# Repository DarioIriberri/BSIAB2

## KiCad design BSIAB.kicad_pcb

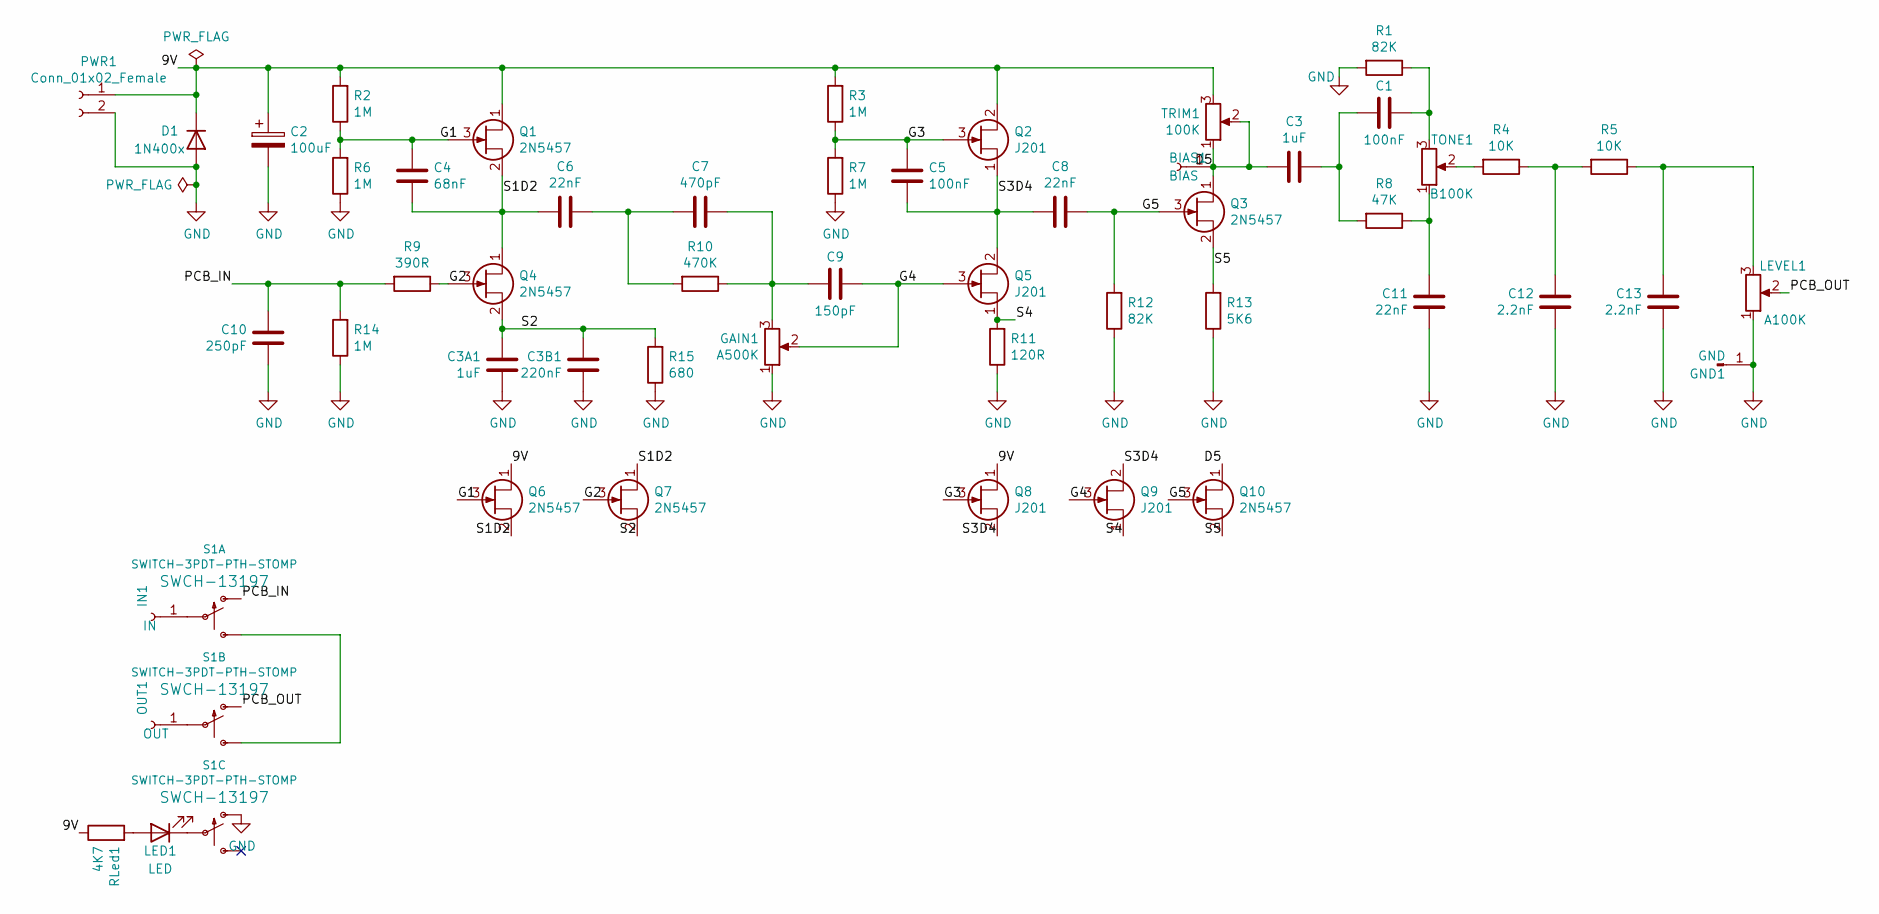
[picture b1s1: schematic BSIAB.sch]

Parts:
BIAS1: BIAS; PinHeader_1x01_P2.54mm_Vertical
C1: 100nF; C_Rect_L9.0mm_W3.4mm_P7.50mm_MKT
C2: 100uF; CP_Radial_D8.0mm_P2.50mm
C3, C3A1: 1uF; C_Rect_L9.0mm_W4.2mm_P7.50mm_MKT
C3B1: 220nF; C_Rect_L9.0mm_W4.2mm_P7.50mm_MKT
C4: 68nF; C_Rect_L9.0mm_W4.2mm_P7.50mm_MKT
C5: 100nF; C_Rect_L9.0mm_W4.2mm_P7.50mm_MKT
C6, C8, C11: 22nF; C_Rect_L9.0mm_W4.2mm_P7.50mm_MKT
C7: 470pF; C_Rect_L7.0mm_W3.5mm_P5.00mm
C9: 150pF; C_Rect_L7.0mm_W3.5mm_P5.00mm
C10: 250pF; C_Rect_L7.0mm_W3.5mm_P5.00mm
C12, C13: 2.2nF; C_Rect_L7.0mm_W3.5mm_P5.00mm
D1: 1N400x; D_A-405_P7.62mm_Horizontal
GAIN1: A500K; Potentiometer_Piher_T-16H_Single_Horizontal
GND1: GND; PinHeader_1x01_P2.54mm_Vertical
IN1: IN; PinHeader_1x01_P2.54mm_Vertical
LED1: LED; LED_D5.0mm
LEVEL1: A100K; Potentiometer_Piher_T-16H_Single_Horizontal
OUT1: OUT; PinHeader_1x01_P2.54mm_Vertical
PWR1: Conn_01x02_Female; JST_EH_B2B-EH-A_1x02_P2.50mm_Vertical
Q1, Q3, Q4: 2N5457; SOT-23
Q2, Q5: J201; SOT-23
Q6, Q7, Q10: 2N5457; TO-92
Q8, Q9: J201; TO-92
R1, R12: 82K; R_Axial_DIN0207_L6.3mm_D2.5mm_P7.62mm_Horizontal
R2, R3, R6, R7, R14: 1M; R_Axial_DIN0207_L6.3mm_D2.5mm_P7.62mm_Horizontal
R4, R5: 10K; R_Axial_DIN0207_L6.3mm_D2.5mm_P7.62mm_Horizontal
R8: 47K; R_Axial_DIN0207_L6.3mm_D2.5mm_P7.62mm_Horizontal
R9: 390R; R_Axial_DIN0207_L6.3mm_D2.5mm_P7.62mm_Horizontal
R10: 470K; R_Axial_DIN0207_L6.3mm_D2.5mm_P7.62mm_Horizontal
R11: 120R; R_Axial_DIN0207_L6.3mm_D2.5mm_P7.62mm_Horizontal
R13: 5K6; R_Axial_DIN0207_L6.3mm_D2.5mm_P7.62mm_Horizontal
R15: 680; R_Axial_DIN0207_L6.3mm_D2.5mm_P7.62mm_Horizontal
RLed1: 4K7; R_Axial_DIN0207_L6.3mm_D2.5mm_P7.62mm_Horizontal
S1: SWITCH-3PDT-PTH-STOMP; STOMP_SWITCH_3PDT
TONE1: B100K; Potentiometer_Piher_T-16H_Single_Horizontal
TRIM1: 100K; Potentiometer_Bourns_3296W_Vertical

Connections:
/9V: C2.1, D1.1 (K), PWR1.1, Q1.1 (D), Q2.2 (D), Q6.1 (D), Q8.1 (D), R2.2, R3.2, RLed1.1, TRIM1.3
/D5: BIAS1.1, C3.1, Q3.1 (D), Q10.1 (D), TRIM1.1, TRIM1.2
/G1: C4.1, Q1.3 (G), Q6.3 (G), R2.1, R6.2
/G2: Q4.3 (G), Q7.3 (G), R9.1
/G3: C5.1, Q2.3 (G), Q8.3 (G), R3.1, R7.2
/G4: C9.1, GAIN1.2, Q5.3 (G), Q9.3 (G)
/G5: C8.1, Q3.3 (G), Q10.3 (G), R12.2
/PCB_IN: C10.2, R9.2, R14.2, S1.P$1 (O)
/PCB_OUT: LEVEL1.2, S1.P$4 (O)
/S1D2: C4.2, C6.2, Q1.2 (S), Q4.1 (D), Q6.2 (S), Q7.1 (D)
/S2: C3A1.2, C3B1.2, Q4.2 (S), Q7.2 (S), R15.2
/S3D4: C5.2, C8.2, Q2.1 (S), Q5.2 (D), Q8.2 (S), Q9.2 (S)
/S4: Q5.1 (S), Q9.1 (D), R11.2
/S5: Q3.2 (S), Q10.2 (S), R13.2
GND: C2.2, C3A1.1, C3B1.1, C10.1, C11.1, C12.1, C13.1, D1.2 (A), GAIN1.1, GND1.1, LEVEL1.1, PWR1.2, R1.2, R6.1, R7.1, R11.1, R12.1, R13.1, R14.1, R15.1, S1.P$7 (O)
unnamed: C1.1, C3.2, R8.2
unnamed: C1.2, R1.1, TONE1.3
unnamed: C6.1, C7.2, R10.2
unnamed: C7.1, C9.2, GAIN1.3, R10.1
unnamed: C11.2, R8.1, TONE1.1
unnamed: C12.2, R4.1, R5.2
unnamed: C13.2, LEVEL1.3, R5.1
unnamed: IN1.1, S1.P$2
unnamed: LED1.1 (K), S1.P$8
unnamed: LED1.2 (A), RLed1.2
unnamed: OUT1.1, S1.P$5
unnamed: R4.2, TONE1.2
unnamed: S1.P$3 (S), S1.P$6 (S)

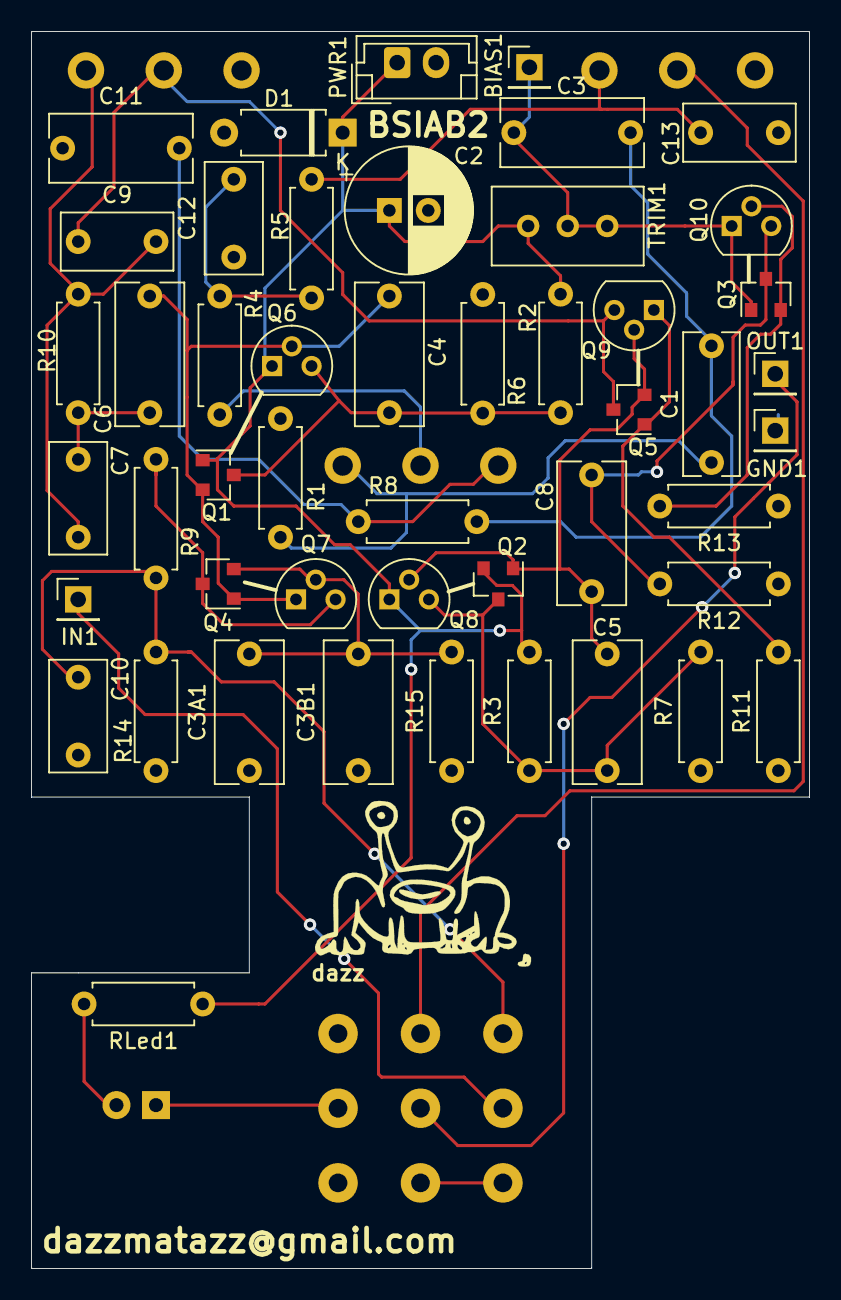
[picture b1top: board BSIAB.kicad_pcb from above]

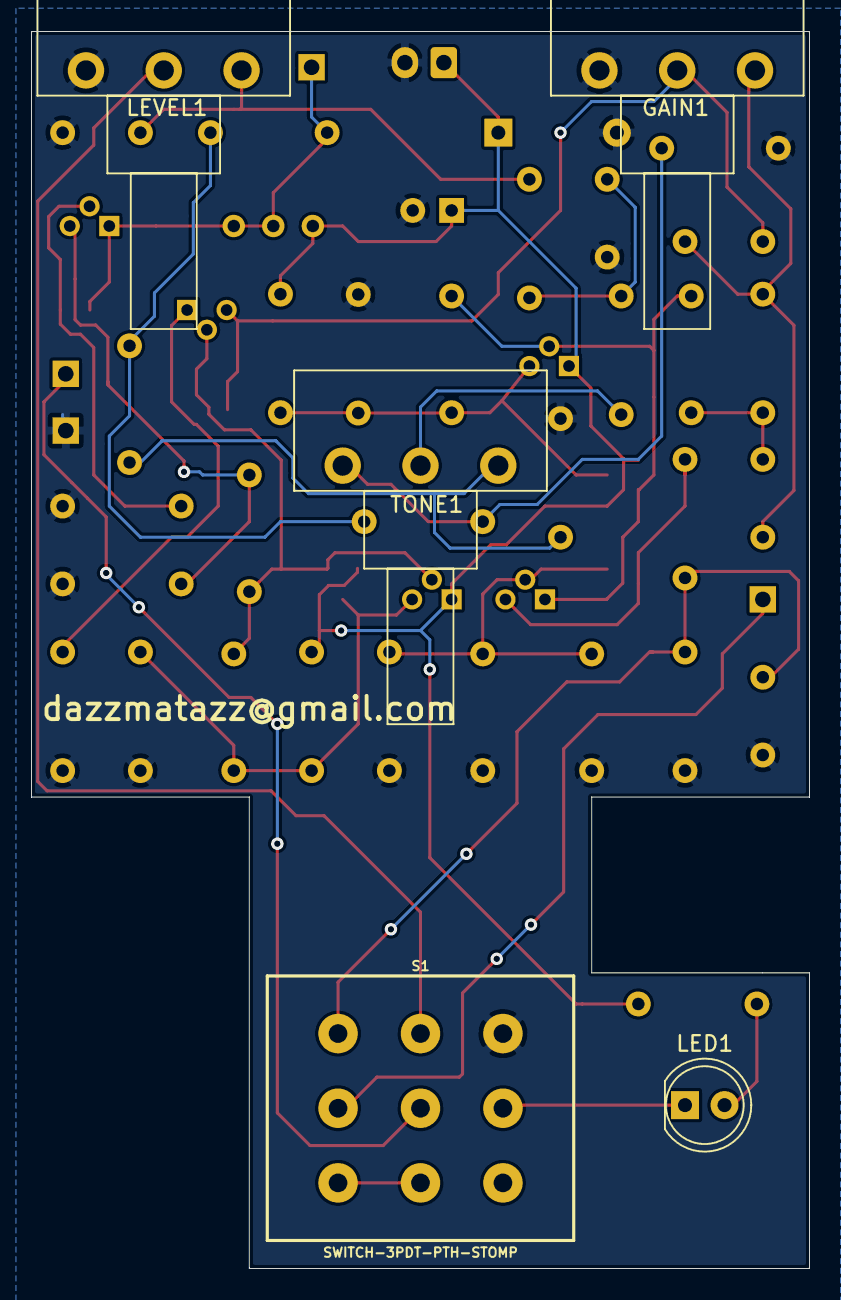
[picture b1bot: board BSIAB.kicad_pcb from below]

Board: 2 copper layers, 50.0 x 79.5 mm, 53 parts (5 on the bottom side), 28 nets.

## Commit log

2022-04-20 Initial Commit.
